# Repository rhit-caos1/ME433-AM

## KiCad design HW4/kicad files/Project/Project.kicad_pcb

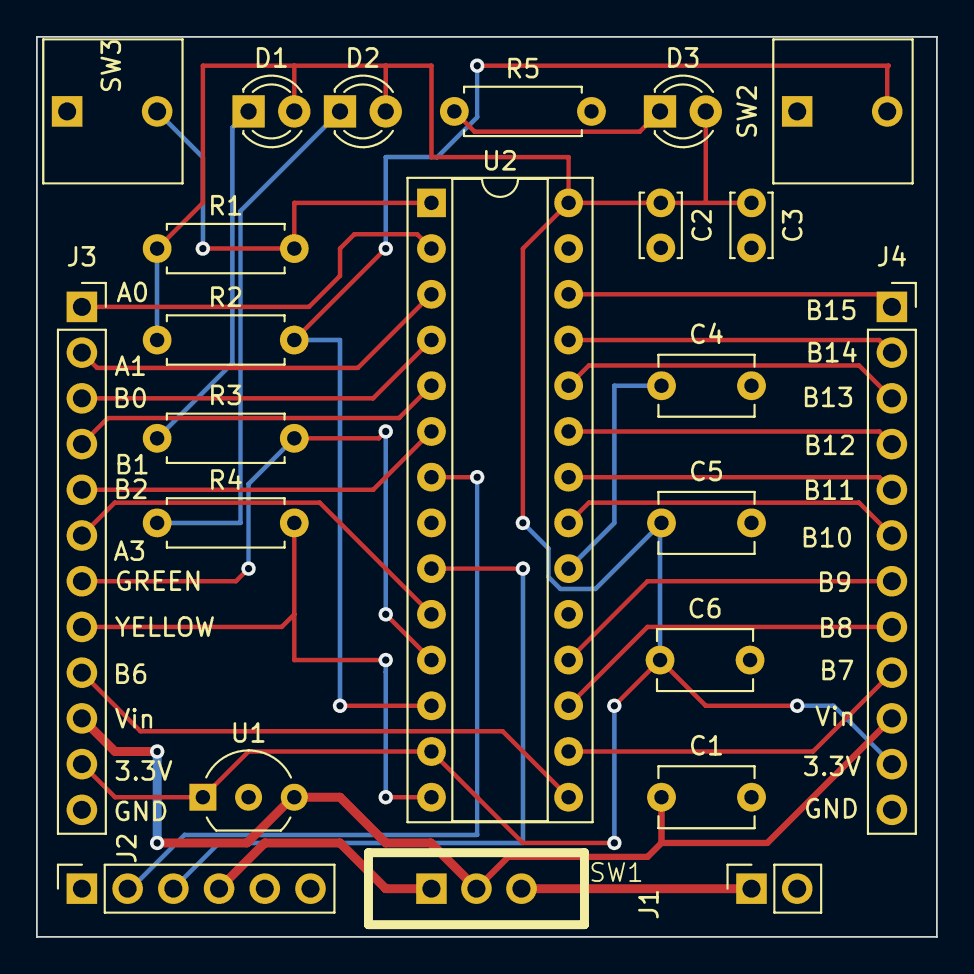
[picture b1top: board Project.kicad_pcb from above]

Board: 2 copper layers, 50.0 x 50.0 mm, 23 parts (0 on the bottom side), 31 nets.

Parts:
C1, C4, C5, C6: 1uF; C_Disc_D5.1mm_W3.2mm_P5.00mm
C2, C3: 0.1uF; C_Disc_D3.4mm_W2.1mm_P2.50mm
D1: GREEN; LED_D3.0mm
D2: YELLOW; LED_D3.0mm
D3: RED; LED_D3.0mm
J1: BATTERY; PinSocket_1x02_P2.54mm_Vertical
J2: CP2102; PinSocket_1x06_P2.54mm_Vertical
J3: Left; PinSocket_1x12_P2.54mm_Vertical
J4: Right; PinSocket_1x12_P2.54mm_Vertical
R1, R2: 10k; R_Axial_DIN0207_L6.3mm_D2.5mm_P7.62mm_Horizontal
R3, R4, R5: 330; R_Axial_DIN0207_L6.3mm_D2.5mm_P7.62mm_Horizontal
SW1: SW_SPDT; slide2
SW2: USER; pushbutton_P2.54mm_Vertical
SW3: MCLR; pushbutton_P2.54mm_Vertical
U1: AP7381-33V; TO-92_Inline_Wide
U2: PIC32MX170F256B; DIP-28_W7.62mm_Socket

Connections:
+3.3V: C2.1, C3.1, C5.1, C6.1, D1.2 (A), D2.2 (A), D3.2 (A), J3.11, J4.11, R1.1, R2.1, U1.1 (VO), U2.13 (Vdd), U2.28 (AVdd)
+5V: J2.4, SW1.1 (A)
/A0: J3.1, U2.2 (A0)
/A1: J3.2, U2.3 (A1)
/A3: J3.6, U2.10 (A3)
/B0: J3.3, U2.4 (B0)
/B1: J3.4, U2.5 (B1)
/B2: J3.5, U2.6 (B2)
/B6: J3.9, U2.15 (B6)
/B7: J4.9, U2.16 (B7)
/B8: J4.8, U2.17 (B8)
/B9: J4.7, U2.18 (B9)
/B10: J4.6, U2.21 (B10)
/B11: J4.5, U2.22 (B11)
/B12: J4.4, U2.23 (B12)
/B13: J4.3, U2.24 (B13)
/B14: J4.2, U2.25 (B14)
/B15: J4.1, U2.26 (B15)
/GREEN: J3.7, R3.2, U2.11 (B4)
/MCLR: R1.2, SW3.2, U2.1 (MCLR)
/U1RX: J2.3, U2.9 (A2)
/U1TX: J2.2, U2.7 (B3)
/USER: R2.2, SW2.2, U2.12 (A4)
/Vin: C1.1, J3.10, J4.10, SW1.2 (B), U1.3 (VI)
/YELLOW: J3.8, R4.2, U2.14 (B5)
GND: C1.2, C2.2, C3.2, C4.2, C5.2, C6.2, J1.2 (GND), J2.6, J3.12, J4.12, R5.2, SW2.1, SW3.1, U1.2 (GND), U2.8 (Vss), U2.19 (Vss), U2.27 (AVss)
unnamed: D1.1 (K), R3.1
unnamed: D2.1 (K), R4.1
unnamed: D3.1 (K), R5.1
unnamed: J1.1 (5V), SW1.3 (C)
unnamed: C4.1, U2.20 (Vcap)

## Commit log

2023-04-05 finished HW2 and 3
2023-04-12 HW4 Kicad files
2023-04-12 add pics
2023-04-19 HW5 update
2023-04-28 HW7 finished
2023-04-28 edit video
2023-04-28 add HW7 short video
2023-04-29 change video
2023-05-04 HW9 finished
2023-05-04 update jpgs
2023-05-09 update HW10
2023-05-12 HW11 update
2023-05-16 update plot
2023-05-18 HW12
2023-06-06 update HW 13 and 14
2023-06-06 Rename REARME.md to README.md
2023-06-06 update HW13 video
2023-06-06 update HW14
2023-06-06 Upload video
2023-06-07 update HW5
2023-06-07 update file for HW15
2023-06-07 update video for HW15
2023-06-08 finish HW16
2023-06-08 update link for HW16
2023-06-08 update image
2023-06-08 update link
